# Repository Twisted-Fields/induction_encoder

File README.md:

Twisted Fields Induction Encoder

Forked from https://github.com/tlalexander/induction_encoder

Run the python script to generate the encoder coils.

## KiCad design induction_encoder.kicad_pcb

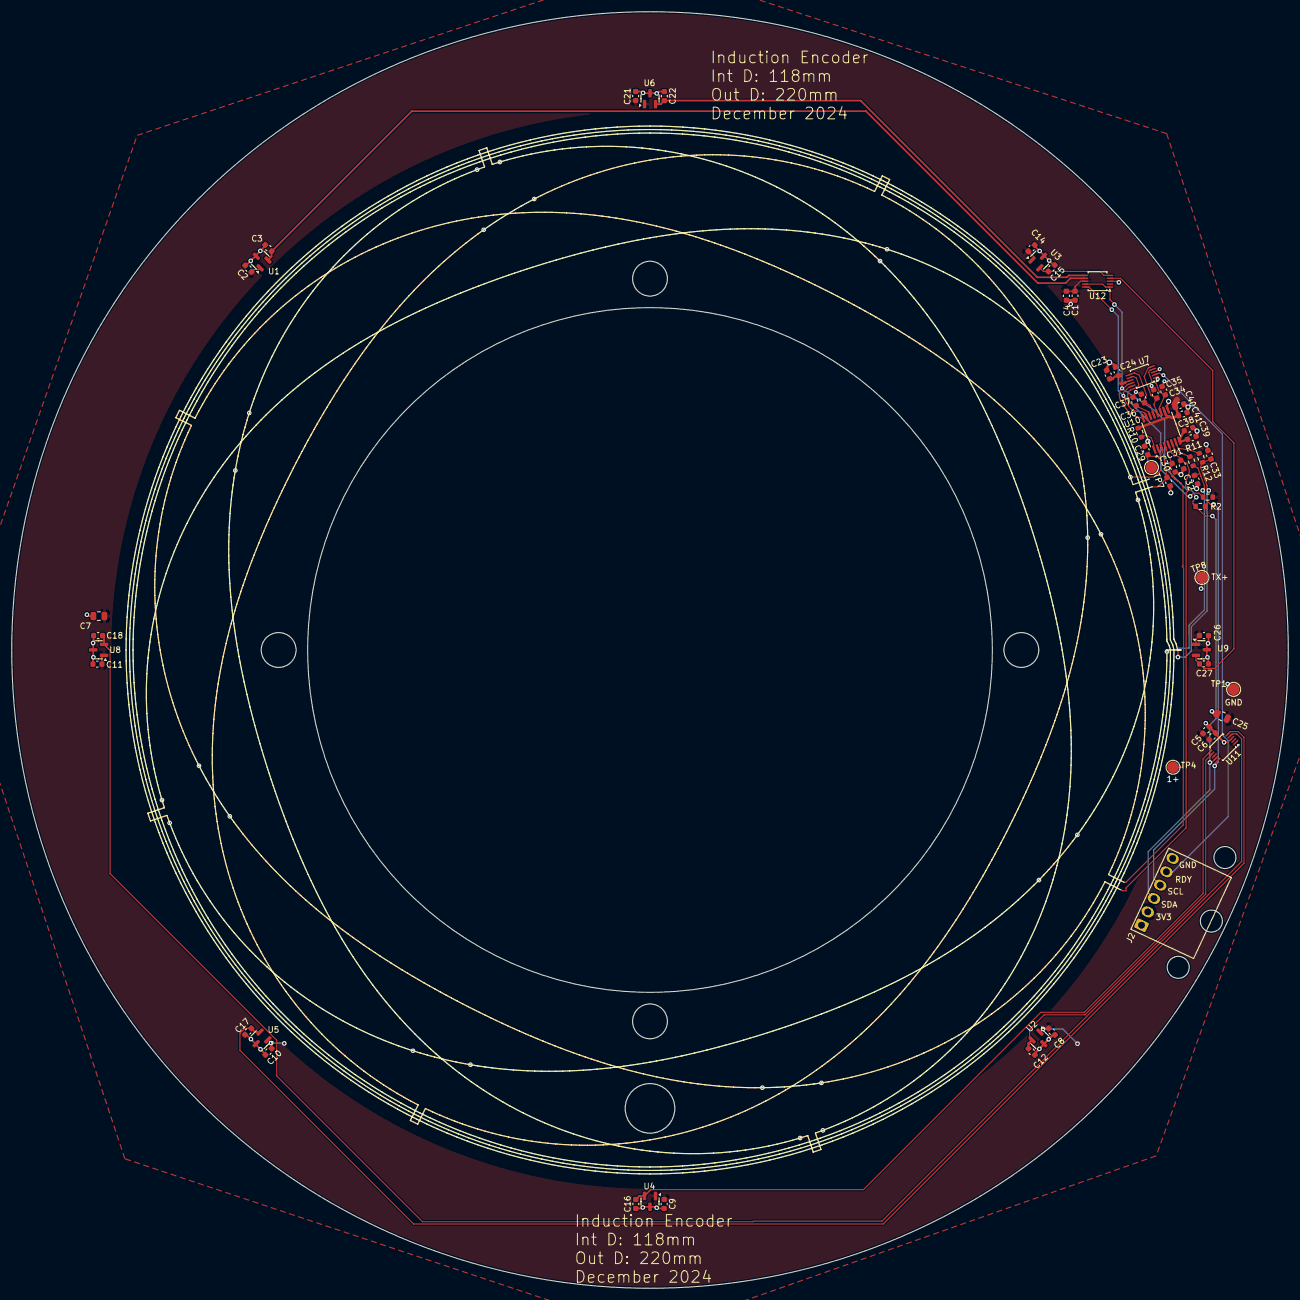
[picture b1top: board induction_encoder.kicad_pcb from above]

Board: 4 copper layers, 220.0 x 220.0 mm, 62 parts (0 on the bottom side), 26 nets.

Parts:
C1, C5, C23: 1u; C_0603_1608Metric
C2, C4, C6, C8, C9, C10, C11, C14, C21, C24, C26: 100n; C_0603_1608Metric
C3, C12, C15, C16, C17, C18, C22, C27: 4.7n; C_0603_1608Metric
C7, C25: 10u; C_0805_2012Metric
C28, C29, C30, C31, C39, C40: 100pF; C_0603_1608Metric
C32, C33: 1.6nF; C_0603_1608Metric
C34, C35, C36, C37: 47nF; C_0603_1608Metric
C38, C41: 470nF; C_0603_1608Metric
J2: Conn_01x06; Ckmtw-W-2510S06P_1x06_P2.54mm_Horizontal
JP1, JP2: SolderJumper_2_Bridged; circuit_bridge
R1, R2: 5.1k; R_0603_1608Metric
R10: 10K; R_0603_1608Metric
R11, R12: 22R; R_0603_1608Metric
TP1, TP4, TP7, TP8: TestPoint; TestPoint_Pad_D2.0mm
U1, U2, U3, U4, U5, U6, U8, U9: MT9105ET; SOT-23
U7, U11, U12: ADS1115IDGS; TSSOP-10_3x3mm_P0.5mm
U10: IPS2200; TSSOP-16_4.4x5mm_P0.65mm

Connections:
1+: C30.2, JP1.2 (B), TP4.1, U10.4 (RX3)
1-: C31.2, JP1.1 (A), U10.5 (RX4)
2: C28.2, C29.2, TP7.1, U10.2 (RX1), U10.3 (RX2)
+3V3: C1.2, C2.1, C4.1, C5.2, C6.1, C7.2, C8.1, C9.1, C10.1, C11.1, C14.1, C21.1, C23.2, C24.1, C25.2, C26.1, C40.2, C41.2, J2.2, R1.1, R2.1, R10.1, U1.1 (VCC), U2.1 (VCC), U3.1 (VCC), U4.1 (VCC), U5.1 (VCC), U6.1 (VCC), U7.8 (VDD), U8.1 (VCC), U9.1 (VCC), U10.10 (VDD), U11.1 (ADDR), U11.8 (VDD), U12.8 (VDD)
/MAG1: C27.2, U9.2 (VOUT), U12.4 (AIN0)
/MAG2: C15.2, U3.2 (VOUT), U12.5 (AIN1)
/MAG3: C22.2, U6.2 (VOUT), U12.6 (AIN2)
/MAG4: C3.2, U1.2 (VOUT), U12.7 (AIN3)
/MAG5: C18.2, U8.2 (VOUT), U11.4 (AIN0)
/MAG6: C17.2, U5.2 (VOUT), U11.5 (AIN1)
/MAG7: C16.2, U4.2 (VOUT), U11.6 (AIN2)
/MAG8: C12.2, U2.2 (VOUT), U11.7 (AIN3)
COS: C35.2, U7.5 (AIN1), U10.12 (COS)
COSN: C34.2, U7.4 (AIN0), U10.11 (COSN)
GND: C1.1, C2.2, C3.1, C4.2, C5.1, C6.2, C7.1, C8.2, C9.2, C10.2, C11.2, C12.1, C14.2, C15.1, C16.1, C17.1, C18.1, C21.2, C22.1, C23.1, C24.2, C25.1, C26.2, C27.1, C28.1, C29.1, C30.1, C31.1, C32.2, C33.2, C34.1, C35.1, C36.1, C37.1, C38.1, C39.1, C40.1, C41.1, J2.6, TP1.1, U1.3 (GND), U2.3 (GND), U3.3 (GND), U4.3 (GND), U5.3 (GND), U6.3 (GND), U7.1 (ADDR), U7.3 (GND), U8.3 (GND), U9.3 (GND), U10.9 (GND), U11.3 (GND), U12.3 (GND)
unnamed: R10.2, U10.1 (CSN_IRQN)
unnamed: R11.2, U10.6 (TX1)
unnamed: R12.2, U10.7 (TX2)
unnamed: C38.2, C39.2, U10.8 (VDDA)
RDY: J2.5, U7.2 (ALERT/RDY)
SCL: J2.4, R1.2, U7.10 (SCL), U10.15 (SCK_SCL), U11.10 (SCL), U12.10 (SCL)
SDA: J2.3, R2.2, U7.9 (SDA), U10.16 (SIO_SDA), U11.9 (SDA), U12.1 (ADDR), U12.9 (SDA)
SIN: C37.2, U7.7 (AIN3), U10.14 (SIN)
SINN: C36.2, U7.6 (AIN2), U10.13 (SINN)
TX+: C32.1, JP2.1 (A), R11.1, TP8.1
TX-: C33.1, JP2.2 (B), R12.1

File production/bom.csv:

Designator,Footprint,Quantity,Value,LCSC Part #
"C1, C23, C5",0603,3,1u,C15849
"C10, C11, C14, C2, C21, C26, C8, C9",0603,8,100n,C14663
"C12, C15, C16, C17, C18, C22, C27, C3",0603,8,4.7n,C106218
"C24, C4, C6",0603,3,100n,
"C25, C7",0805,2,10u,C15850
"C28, C29, C30, C31, C39, C40",0603,6,100pF,C14665
"C32, C33",0603,2,1.6nF,C437532
"C34, C35, C36, C37",0603,4,47nF,C285123
"C38, C41",0603,2,470nF,C1623
J2,Ckmtw-W-2510S06P_1x06_P2.54mm_Horizontal,1,Conn_01x06,C2982045
"R1, R2",0603,2,5.1k,C26000
R10,0603,1,10K,C25804
"R11, R12",0603,2,22R,C5139508
"U1, U2, U3, U4, U5, U6, U8, U9",SOT-23,8,MT9105ET,C967861
U10,TSSOP-16_4.4x5mm_P0.65mm,1,IPS2200,
"U11, U12, U7",TSSOP-10_3x3mm_P0.5mm,3,ADS1115IDGS,C37593

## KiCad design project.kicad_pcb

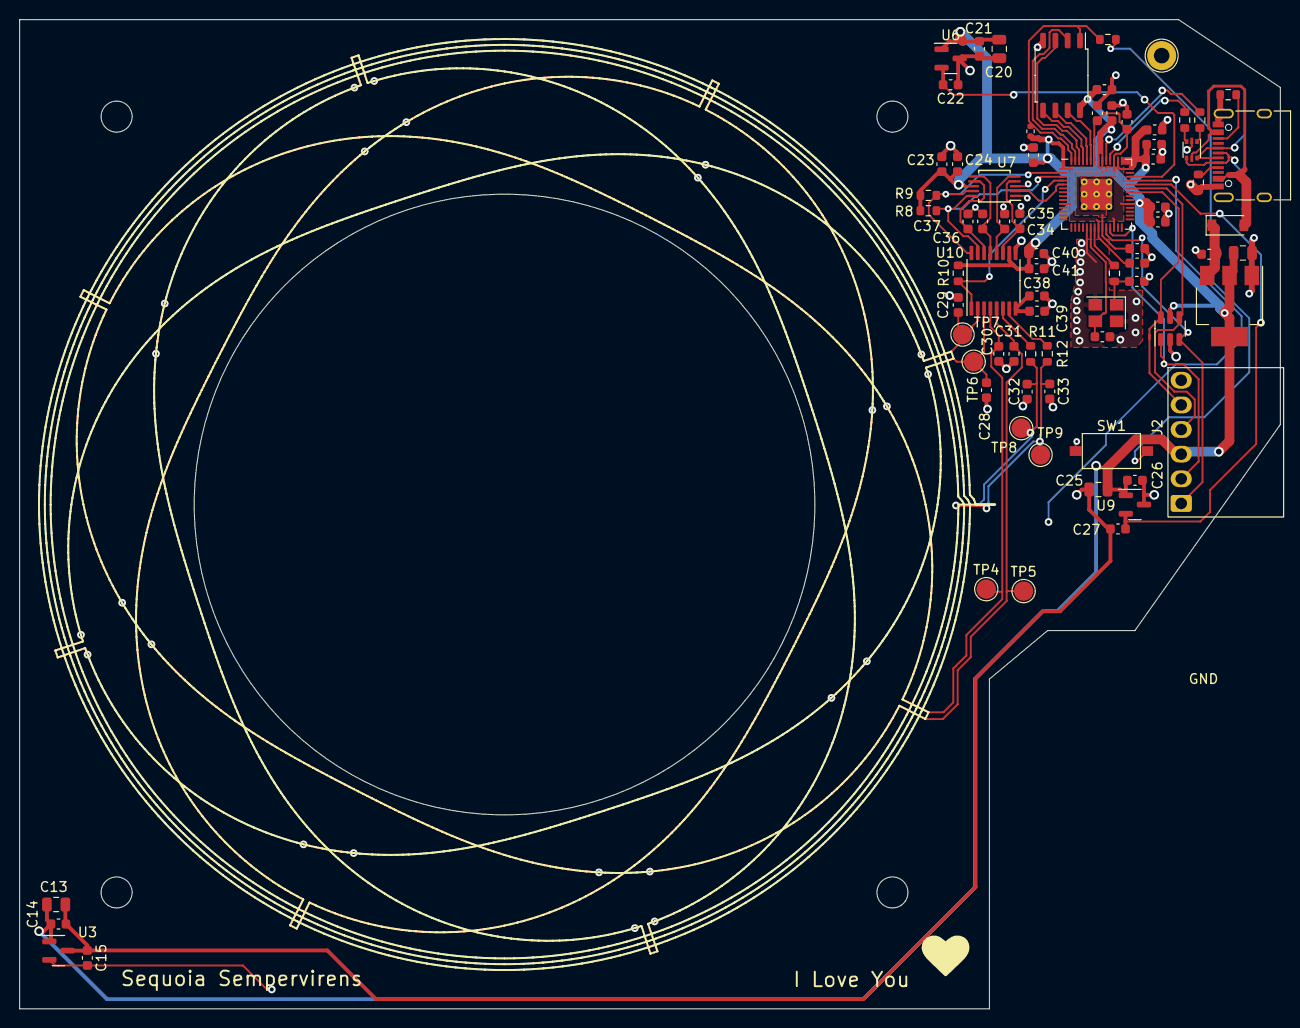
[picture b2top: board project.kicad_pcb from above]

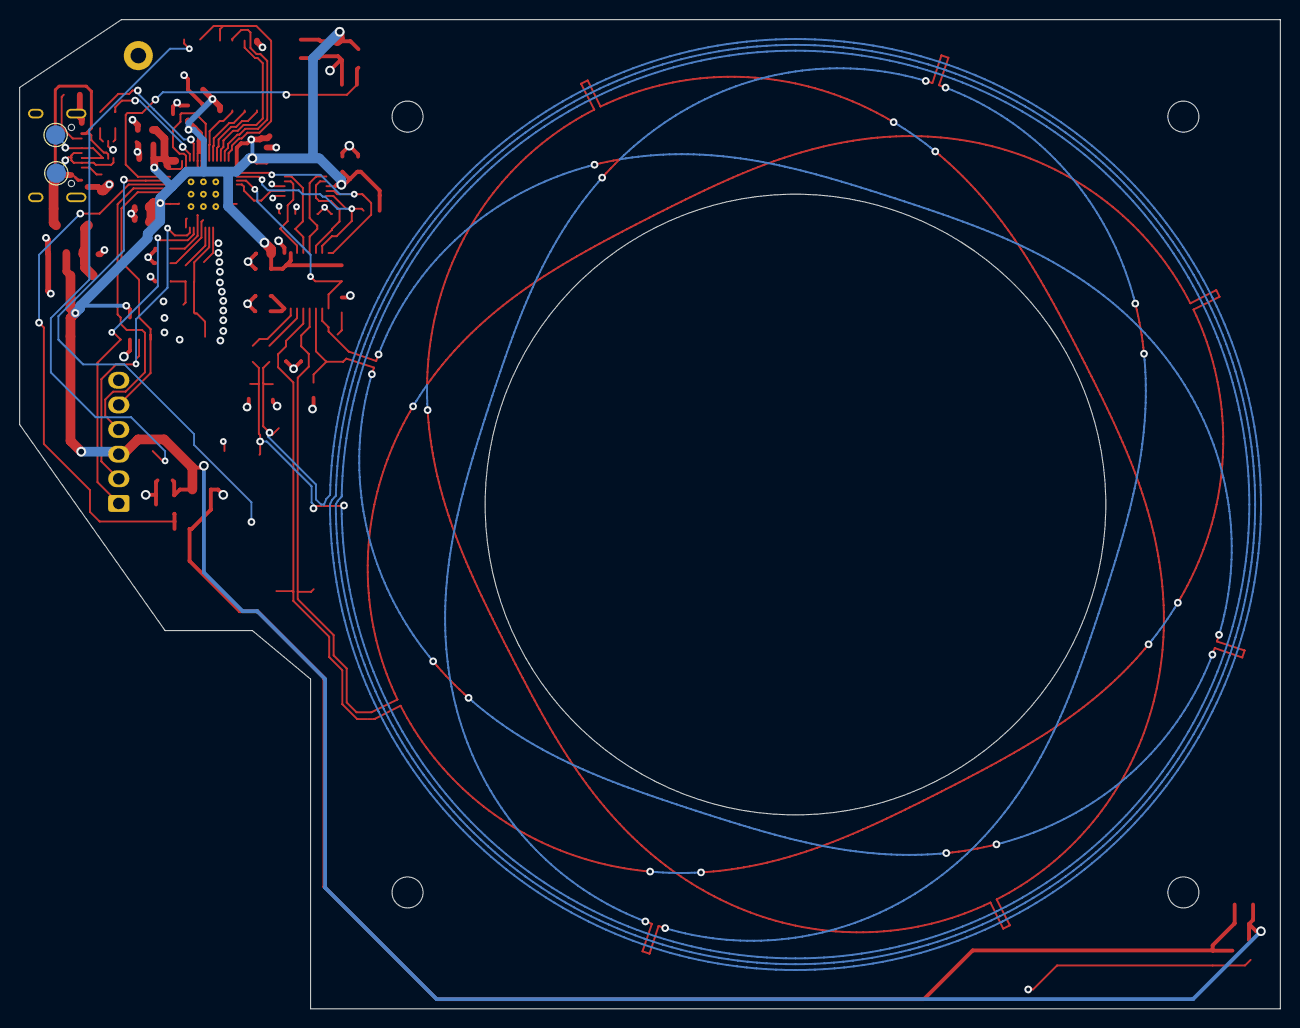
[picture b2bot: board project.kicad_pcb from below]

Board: 4 copper layers, 130.0 x 102.0 mm, 83 parts (2 on the bottom side), 46 nets.

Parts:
C1, C2, C3, C4, C5, C6, C7, C8, C9, C12, C14, C21, C24, C26: 100n; C_0603_1608Metric
C10, C11, C16, C23: 1u; C_0603_1608Metric
C13, C17, C20, C25: 10u; C_0805_2012Metric
C15, C22, C27: 4.7n; C_0603_1608Metric
C18, C19: 20p; C_0603_1608Metric
C28, C29, C30, C31, C39, C40: 100pF; C_0603_1608Metric
C32, C33: 1.6nF; C_0603_1608Metric
C34, C35, C36, C37: 47nF; C_0603_1608Metric
C38, C41: 470nF; C_0603_1608Metric
D1: B5819W SL; D_SOD-123
H1, H2, H3, H4: MountingHole; MountingHole_3.2mm_M3
J1: CPU2 USB; USB_C_Receptacle_XKB_U262-16XN-4BVC11
J2: Conn_01x06; Ckmtw-W-2510S06P_1x06_P2.54mm_Horizontal
JP1, JP2: SolderJumper_2_Bridged; circuit_bridge
R1: DNS; R_0402_1005Metric
R2, R7: 1.1k; R_0603_1608Metric
R3, R4: 27; R_0603_1608Metric
R5, R6: 5.1k; R_0603_1608Metric
R8, R9, R10: 10k; R_0603_1608Metric
R11, R12: 22R; R_0603_1608Metric
SW1: SW_MEC_5G; SW_TS_1101_C_W
TP1, TP2, TP4, TP5, TP6, TP7, TP8, TP9: TestPoint; TestPoint_Pad_D2.0mm
TP3: TestPoint; TestPoint_Loop_D2.60mm_Drill1.6mm_Beaded
U1: W25Q128JVSIQ; SOIC-8_5.23x5.23mm_P1.27mm
U2: USBLC6-2P6; SOT-666
U3, U6, U9: MT9105ET; SOT-23
U4: TLV1117LV33DCYR; SOT-223-3_TabPin2
U5: RP2040; RP2040-QFN-56
U7: ADS1115IDGS; TSSOP-10_3x3mm_P0.5mm
U8: USBLC6-4SC6; SOT-23-6
U10: IPS2200; TSSOP-16_4.4x5mm_P0.65mm
Y1: 12MHz; Crystal_SMD_3225-4Pin_3.2x2.5mm

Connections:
1+: C30.2, JP1.2 (B), TP4.1, U10.4 (RX3)
1-: C31.2, JP1.1 (A), TP5.1, U10.5 (RX4)
2: C28.2, C29.2, TP6.1, TP7.1, U10.2 (RX1), U10.3 (RX2)
+3V3: C3.1, C4.1, C5.1, C6.1, C7.1, C8.1, C9.1, C11.1, C12.1, C13.2, C14.1, C17.1, C20.2, C21.1, C23.2, C24.1, C25.2, C26.1, C40.2, C41.2, J2.3, R1.1, R8.1, R9.1, R10.1, U1.8 (VCC), U3.1 (VCC), U4.2 (VO), U5.1 (IOVDD), U5.10 (IOVDD), U5.22 (IOVDD), U5.26 (RUN), U5.33 (IOVDD), U5.42 (IOVDD), U5.43 (ADC_AVDD), U5.44 (VREG_IN), U5.48 (USB_VDD), U5.49 (IOVDD), U6.1 (VCC), U7.8 (VDD), U8.5 (VBUS), U9.1 (VCC), U10.10 (VDD)
+5V: C16.1, D1.1 (K), U4.3 (VI)
/1V1: C1.1, C2.1, C10.1, U5.23 (DVDD), U5.45 (VREG_VOUT), U5.50 (DVDD)
/QSPI_SCLK_2: U1.6 (CLK), U5.52 (QSPI_SCLK)
/QSPI_SD0_2: U1.5 (DI(IO0)), U5.53 (QSPI_SD0)
/QSPI_SD1_2: U1.2 (DO(IO1)), U5.55 (QSPI_SD1)
/QSPI_SD2_2: U1.3 (IO2), U5.54 (QSPI_SD2)
/QSPI_SD3_2: U1.7 (IO3), U5.51 (QSPI_SD3)
/QSPI_SS_2: R1.2, R2.1, U1.1 (~CS), U5.56 (QSPI_SS)
/RXI_2: J2.4, U5.37 (GPIO25), U8.4 (I/O3)
/SWCLK_2: J2.1, U5.24 (SWCLK), U8.3 (I/O2)
/SWD_2: J2.2, U5.25 (SWD), U8.1 (I/O1)
/TXO_2: J2.5, U5.36 (GPIO24), U8.6 (I/O4)
/USB_DN_2: R4.2, U5.46 (USB_DM)
/USB_DP_2: R3.2, U5.47 (USB_DP)
/USB_D_2+: J1.A6 (D+), J1.B6 (D+), TP2.1, U2.6 (I/O1)
/USB_D_2-: J1.A7 (D-), J1.B7 (D-), TP1.1, U2.4 (I/O2)
/~USB_BOOT_2: R2.2, SW1.2
COS: C35.2, U7.5 (AIN1), U10.12 (COS)
COSN: C34.2, U7.4 (AIN0), U10.11 (COSN)
GND: C1.2, C2.2, C3.2, C4.2, C5.2, C6.2, C7.2, C8.2, C9.2, C10.2, C11.2, C12.2, C13.1, C14.2, C15.1, C16.2, C17.2, C18.2, C19.2, C20.1, C21.2, C22.1, C23.1, C24.2, C25.1, C26.2, C27.1, C28.1, C29.1, C30.1, C31.1, C32.2, C33.2, C34.1, C35.1, C36.1, C37.1, C38.1, C39.1, C40.1, C41.1, J1.A1 (GND), J1.A12 (GND), J1.B1 (GND), J1.B12 (GND), J1.S1 (SHIELD), J2.6, R5.1, R6.2, SW1.1, TP3.1, U1.4 (GND), U2.2 (GND), U3.3 (GND), U4.1 (GND), U5.19 (TESTEN), U5.57 (GND), U6.3 (GND), U7.1 (ADDR), U7.3 (GND), U8.2 (GND), U9.3 (GND), U10.9 (GND), Y1.2, Y1.4
IRQN: R10.2, U5.4 (GPIO2), U10.1 (CSN_IRQN)
MAG1: C27.2, U5.38 (GPIO26_ADC0), U9.2 (VOUT)
MAG2: C15.2, U3.2 (VOUT), U5.39 (GPIO27_ADC1)
MAG3: C22.2, U5.40 (GPIO28_ADC2), U6.2 (VOUT)
unnamed: C19.1, R7.2, Y1.1
unnamed: J1.A5 (CC1), R5.2
unnamed: J1.B5 (CC2), R6.1
unnamed: R3.1, U2.1 (I/O1)
unnamed: R4.1, U2.3 (I/O2)
unnamed: C18.1, U5.20 (XIN), Y1.3
unnamed: R7.1, U5.21 (XOUT)
unnamed: R11.2, U10.6 (TX1)
unnamed: R12.2, U10.7 (TX2)
unnamed: C38.2, C39.2, U10.8 (VDDA)
RDY: U5.5 (GPIO3), U7.2 (ALERT/RDY)
SCL: R8.2, U5.3 (GPIO1), U7.10 (SCL), U10.15 (SCK_SCL)
SDA: R9.2, U5.2 (GPIO0), U7.9 (SDA), U10.16 (SIO_SDA)
SIN: C37.2, U7.7 (AIN3), U10.14 (SIN)
SINN: C36.2, U7.6 (AIN2), U10.13 (SINN)
TX+: C32.1, JP2.1 (A), R11.1, TP8.1
TX-: C33.1, JP2.2 (B), R12.1, TP9.1
VBUS: D1.2 (A), J1.A4 (VBUS), J1.A9 (VBUS), J1.B4 (VBUS), J1.B9 (VBUS), U2.5 (VBUS)

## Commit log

2024-01-18 Initial commit, first encoder version.
2024-02-06 rename files. check in before enlarging diameter
2024-02-06 Add license file.
2024-02-06 Updated to larger encoder size.
2024-02-06 Add readme with image
2024-09-16 changes for the 170mm design
2024-11-12 initial layout for 100-170mm induction encoder
2024-11-13 layout finished for 100-170mm induction encoder
2024-11-14 100-170mm version ordered November 2024
2024-12-23 autogenerated files
2024-12-23 starting layout for 118-220mm induction encoder
2024-12-23 118-220 layout progress
2024-12-26 118-220 boards ready to order
